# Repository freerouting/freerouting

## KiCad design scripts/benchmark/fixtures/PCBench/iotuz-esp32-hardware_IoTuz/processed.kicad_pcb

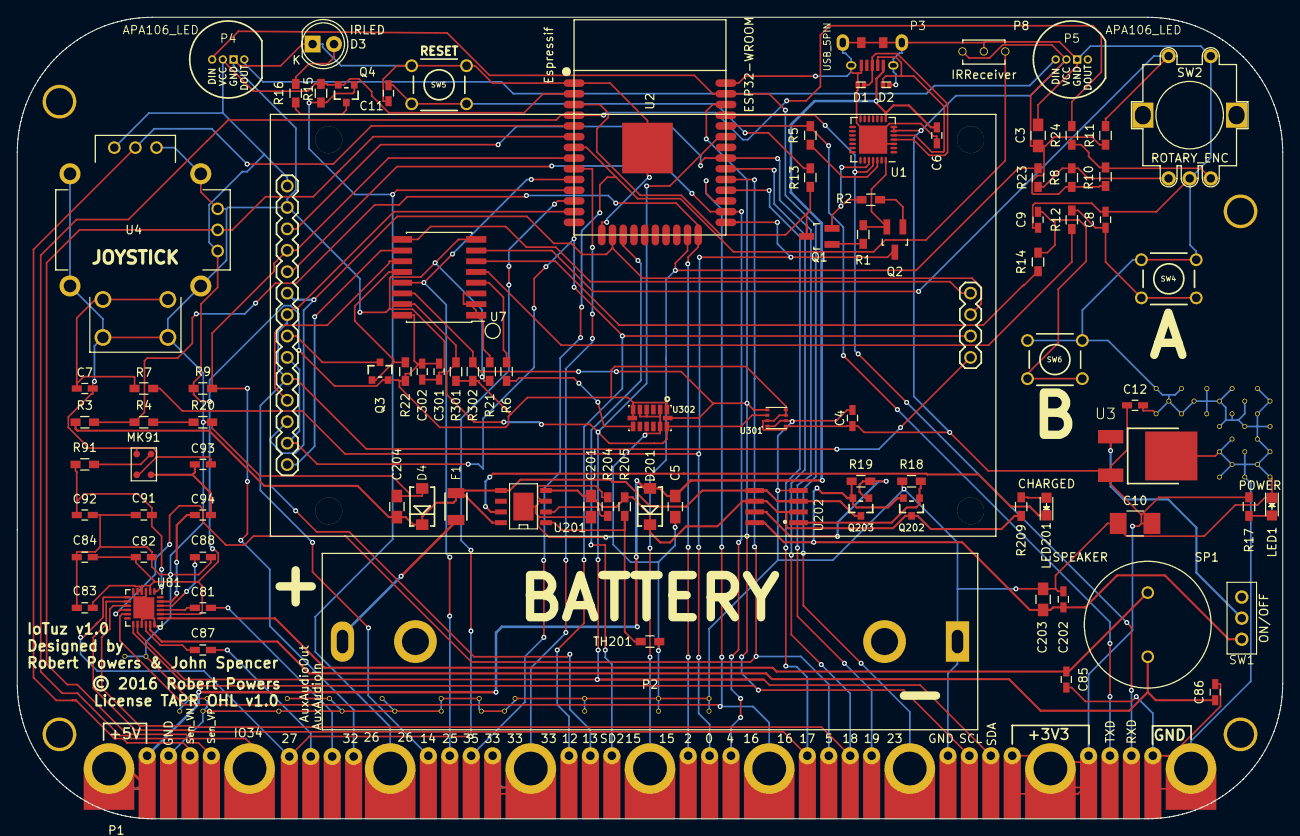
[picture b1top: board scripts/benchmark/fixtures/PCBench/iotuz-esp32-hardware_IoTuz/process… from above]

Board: 2 copper layers, 150.0 x 95.0 mm, 153 parts (0 on the bottom side), 82 nets.

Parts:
C3, C5, C201, C203, C204: 10uF 16V; C_0805_HandSoldering
C4, C6, C12, C202: 0.1uF; C_0603_HandSoldering
C7, C8, C9: 1nF; C_0603_HandSoldering
C10: 100uF 6.3V X5R; C_1210_HandSoldering
C11, C81, C87, C94, C301, C302: 1uF; C_0603_HandSoldering
C82, C83, C84, C88, C91: 4.7uF; C_0603_HandSoldering
C85, C86, C92, C93: 33pF 1%; C_0603_HandSoldering
D1, D2: ESD05V88D-LC; SOD-882
D3: IRLED; LED-5MM
D4, D201: SS14; DIODE_SMA
F1: 1A PTC; 1210
LED1: POWER; LED_0805
LED201: CHARGED; LED_0805
MK91: SPU0410HR5H; MEMSMicrophone-SMT-SPU0410HR5H‐PB
MP1, MP2, MP3, MP4: M3; MountingHole_3.2mm_M3.IoTuz
Noname_1, Noname_2, Noname_3, Noname_4, Noname_5, Noname_6, Noname_7, Noname_8, Noname_9, Noname_10, Noname_11, Noname_12, Noname_13, Noname_14, Noname_15, Noname_16, Noname_17, Noname_18, Noname_19, Noname_20, Noname_21, Noname_22, Noname_23, Noname_24, Noname_25, Noname_26, Noname_27, Noname_28, Noname_29, Noname_30, Noname_31, Noname_32, Noname_33, Noname_34, Noname_35, Noname_36, Noname_37, Noname_38, Noname_39, Noname_40, Noname_41, Noname_42, Noname_43, Noname_44, Noname_45, Noname_46, Noname_47, Noname_48, Noname_49, Noname_50, Noname_51, Noname_52: via.0.6mm-drill.0.4mm
P1: ALLIGATOR_X39; alligator_pads.x39.shortened
P2: BATTERY; BH-18650
P3: USB_5PIN; USB-MICRO-5pin_PTHMOUNT-Amphenol.10118194-0001LF
P4, P5: APA106_LED; LED_8MM_APA-106
P8: IRReceiver; TSOP38238.IRReceiver
Q1, Q2: S8050; SOT-23_Handsoldering
Q3, Q4, Q202, Q203: FDN340P; SOT23_FET
R1, R2: 12K(1%); R_0603_HandSoldering
R3: 1M; R_0603_HandSoldering
R4, R18, R19: 100K; R_0603_HandSoldering
R5, R7, R12, R13, R14, R17, R209: 470R(1%); R_0603_HandSoldering
R6, R8, R9, R10, R11, R15, R20, R21, R22, R23, R24: 10K; R_0603_HandSoldering
R16: 22R; R_0603_HandSoldering
R91: 1K; R_0603_HandSoldering
R204: 3.6K 1%; R_0603_HandSoldering
R205: 7.15K 1%; R_0603_HandSoldering
R301, R302: 4.7K; R_0603_HandSoldering
SP1: SPEAKER; CVS-1508.Speaker.PCPins
SW1: ON/OFF; SS12D00
SW2: ROTARY_ENC; EC11
SW4: A; SW_PUSHBUTTON_PTH
SW5: RESET; SW_PUSHBUTTON_PTH
SW6: B; SW_PUSHBUTTON_PTH
TH201: 10K NTC; R_0603_HandSoldering
U1: CP2102; QFN-28-1EP_5x5mm_Pitch0.5mm
U2: ESP32-WROOM
U3: NCP5501; DPAK3.NCP5501
U4: JOYSTICK; JOYSTICK_W_BUTTON
U6: ili9341.TouchLCD.Red.NoName; lcdtouchscreen.2.8inch-red.no-name.ili9341-xpt2046
U7: PCF8574; PCF8574.SOIC-16W_Pitch1.27mm
U81: NAU8814; NAU8814_QFN-24_4x4mm_Pitch0.5mm_EPAD
U201: CN3063; CN3063_SOIC8_EP
U202: MCP6002; SO08_4mm
U301: BME280
U302: ADXL345

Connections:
+3V3: C3.1, C4.1, C10.2, C12.1, C82.1, C83.1, C84.1, C301.1, C302.1, P1.5, P1.6, P1.7, P4.2, P5.2, P8.3, Q3.S, Q4.S, R8.2, R9.2, R10.2, R11.1, R15.1, R17.2, R22.1, R301.1, R302.1, U1.6, U1.7, U2.2, U3.3, U4.X1, U4.Y3, U6.1, U7.16, U81.2, U81.4, U81.5, U81.20, U301.2, U301.5, U301.6, U301.8, U302.1, U302.6, U302.7
+5V: C5.1, C6.1, D201.A, P1.38, P1.39, P3.1, U1.8
/ACCEL_INT: R6.1, U7.4
/A_Btn: R12.1, U7.5
/Audio/AUX: C81.1, U81.21
/Audio/MIC-: C94.1, U81.23
/Audio/MICBias: C91.1, C92.1, R91.2, U81.1
/Audio/Speaker+: C86.1, SP1.2, U81.17
/Audio/Speaker-: C85.1, SP1.1, U81.19
/AuxAudioIn: C81.2, P1.31
/BAT+: C204.1, D4.K, F1.2, Q203.D, R3.1, U201.5, U201.8, U202.3, U202.5
/BL_Control: Q3.G, R22.2, U7.12
/B_Btn: R14.1, U7.6
/DTR: Q2.2, R1.2, U1.28
/EN: Q1.3, R13.1, U2.3
/Enc_Btn: R11.2, SW2.4, U7.7
/I2C Sensors/ADXL_INT: R6.2, U302.8
/I2C_SCL: P1.9, R302.2, U2.36, U7.14, U81.13, U301.4, U302.14
/I2C_SDA: P1.8, R301.2, U2.33, U7.15, U81.14, U301.3, U302.13
/IO0: P1.18, Q2.3, R7.2, U2.25
/IO2: P1.19, R3.2, R4.2, U2.24
/IO4: P1.17, U2.26, U6.5
/IO5: P1.14, U2.29, U81.10
/IO12: P1.23, U2.14, U6.9, U6.13, U6.17
/IO13: P1.22, U2.16, U6.6, U6.12, U6.16
/IO14: P1.28, U2.13, U6.7, U6.10, U6.18
/IO15: P1.20, R23.2, U2.23
/IO16: P1.16, U2.27, U81.11
/IO17: P1.15, U2.28, U81.8
/IO18: P1.13, U2.30, U81.9
/IO19: P1.12, U2.31, U6.3
/IO23: P1.11, P4.1, U2.37
/IO25: P1.27, U2.10, U7.13
/IO26: P1.29, Q4.G, R15.2, U2.11
/IO27: P1.33, U2.12, U81.7
/IO32: P1.30, R9.1, U2.8, U6.4
/IO33: P1.24, P1.25, U2.9
/IO34: P1.34, U2.6, U4.X2
/IO35: P1.26, P8.1, U2.7
/MonoAudioOut: C87.1, P1.32
/Power/3.3V: C202.1, C203.1, Q202.S, Q203.S, R19.1, SW1.1, U202.8
/Power/3.3V_SWITCH: SW1.2, U3.1
/Power/GBAT: Q203.G, R19.2, U202.7
/Power/GIN: Q202.G, R18.1, U202.1
/Power/VIN: C201.1, D201.K, Q202.D, R205.1, R209.2, U201.4, U202.2, U202.6
/Power/~CHRG: LED201.1, U201.7
/RTS: Q1.2, R2.2, U1.24
/RXD: P1.3, U1.25, U2.35
/SD2: P1.21, U2.17
/SD_Sel: U6.15, U7.9
/Sensor_VN: P1.36, U2.5, U4.Y2
/Sensor_VP: P1.35, R24.2, U2.4
/TXD: P1.4, R5.1, U2.34
/Touch_INT: U6.14, U7.10
/Touch_Sel: U6.11, U7.11
/USB_D+: D1.2, P3.3, U1.4
/USB_D-: D2.2, P3.2, U1.5
GND: C3.2, C4.2, C5.2, C6.2, C7.2, C8.2, C9.2, C10.1, C11.2, C12.2, C82.2, C83.2, C84.2, C85.2, C86.2, C88.1, C91.2, C92.2, C93.2, C201.2, C202.2, C203.2, C204.2, C301.2, C302.2, D1.1, D2.1, D3.1, D4.A, LED1.1, MK91.2, MK91.3, Noname_1.1, Noname_2.1, Noname_3.1, Noname_4.1, Noname_5.1, Noname_6.1, Noname_7.1, Noname_8.1, Noname_9.1, Noname_10.1, Noname_11.1, Noname_12.1, Noname_13.1, Noname_14.1, Noname_15.1, Noname_16.1, Noname_17.1, Noname_18.1, Noname_19.1, Noname_20.1, Noname_21.1, Noname_22.1, Noname_23.1, Noname_24.1, Noname_25.1, Noname_26.1, Noname_27.1, Noname_28.1, Noname_29.1, Noname_30.1, Noname_31.1, Noname_32.1, Noname_33.1, Noname_34.1, Noname_35.1, Noname_36.1, Noname_37.1, Noname_38.1, Noname_39.1, Noname_40.1, Noname_41.1, Noname_42.1, Noname_43.1, Noname_44.1, Noname_45.1, Noname_46.1, Noname_47.1, Noname_48.1, Noname_49.1, Noname_50.1, Noname_51.1, Noname_52.1, P1.1, P1.2, P1.10, P1.37, P2.1, P3.5, P3.SHLD, P4.3, P5.3, P8.2, R18.2, R20.1, R21.2, R204.2, SW2.2, SW2.5, SW4.1, SW5.1, SW6.1, TH201.2, U1.3, U1.29, U2.1, U2.15, U2.38, U2.39, U3.2, U4.SH, U4.SW2, U4.X3, U4.Y1, U6.2, U7.8, U81.3, U81.6, U81.15, U81.18, U81.25, U201.3, U201.PAD, U202.4, U301.1, U301.7, U302.2, U302.4, U302.5, U302.12
unnamed: C7.1, R7.1, U4.SW1
unnamed: C8.1, R12.2, SW4.2
unnamed: C9.1, R14.2, SW6.2
unnamed: C11.1, R13.2, SW5.2
unnamed: C87.2, U81.16
unnamed: C88.2, U81.22
unnamed: C93.1, C94.2, MK91.4
unnamed: D3.2, R16.2
unnamed: F1.1, P2.2
unnamed: LED1.2, R17.1
unnamed: LED201.2, R209.1
unnamed: MK91.1, R91.1
unnamed: P4.4, P5.1
unnamed: Q1.1, R1.1
unnamed: Q2.1, R2.1
unnamed: Q3.D, U6.8
unnamed: Q4.D, R16.1
unnamed: R5.2, U1.26
unnamed: R10.1, R24.1, SW2.3
unnamed: R4.1, R20.2
unnamed: R21.1, U7.1, U7.2, U7.3
unnamed: R8.1, R23.1, SW2.1
unnamed: R204.1, U201.2
unnamed: R205.2, TH201.1, U201.1

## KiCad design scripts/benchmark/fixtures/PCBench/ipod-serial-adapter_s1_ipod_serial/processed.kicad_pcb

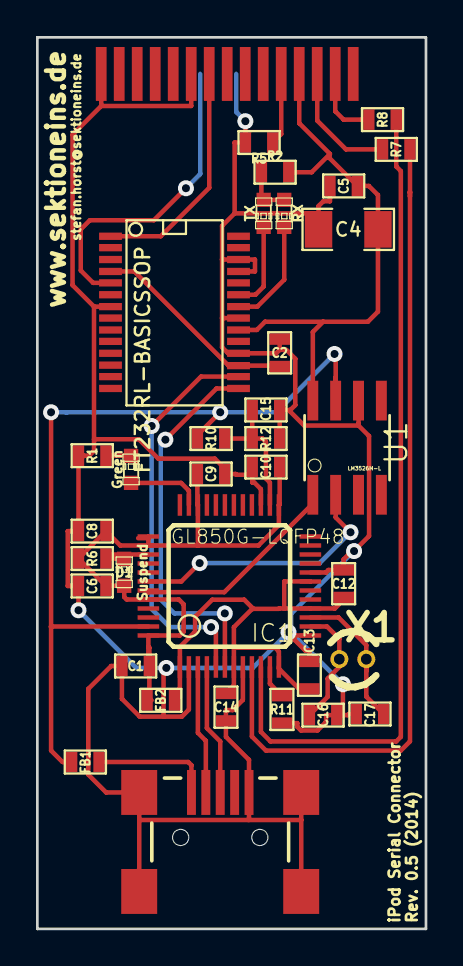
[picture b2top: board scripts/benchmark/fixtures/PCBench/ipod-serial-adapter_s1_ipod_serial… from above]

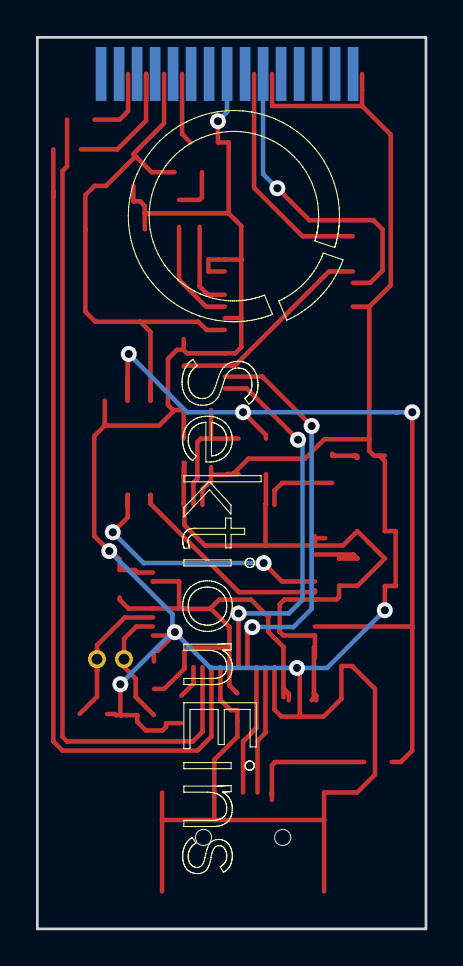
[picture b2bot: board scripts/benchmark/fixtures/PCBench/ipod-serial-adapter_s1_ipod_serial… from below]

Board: 2 copper layers, 21.6 x 49.5 mm, 36 parts (2 on the bottom side), 30 nets.

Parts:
C1: 10uF/10V; SM0603
C2, C5, C6, C8, C9, C10, C12, C13, C14: 100nF; SM0603
C4: 100uF; SM1206
C15: 1uF; SM0603
C16, C17: 20pF; SM0603
D1: Suspend; LED-0603
D2: Green; LED-0603
D3: RX; LED-0603
D4: TX; LED-0603
FB1, FB2: FILTER; SM0603
IC1: GL850G-LQFP48; LQFP48
J1: USB-MINIB-5PIN; USB-MINIB
P1: IPOD_CONNECTOR_MALE; IPOD_MALE_CONNECTOR
R1: 470R; SM0603
R2: 270R; SM0603
R5: 470K; SM0603
R6: 100K; SM0603
R7, R8: 0R; SM0603
R10: 10K; SM0603
R11: 680R; SM0603
R12: 47K; SM0603
SektionEinsLogo: VAL**; SektionEinsLogo
U1: LM3526M-L; SO08
U2: FT232RL-BASICSSOP; SSOP-28
X1: 12 Mhz; Crystal_Round_Vertical_3mm

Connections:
+5V: C4.1, C5.2, P1.23, R2.1, U1.8, U2.20
/HUB_IPOD_GREEN: D2.1, IC1.35
/IPOD_USB_D+: IC1.10, R8.2
/IPOD_USB_D-: IC1.9, R7.2
/OVCUR1: IC1.42, U1.2
/PWREN1: IC1.43, U1.1
/SERIAL_RX: P1.12, U2.5
/SERIAL_RX_LED: D3.2, U2.22
/SERIAL_TX: P1.13, U2.1
/SERIAL_TX_LED: D4.2, U2.23
/SERIAL_USB_D+: IC1.6, U2.15
/SERIAL_USB_D-: IC1.5, U2.16
/USB_D+: IC1.4, J1.D+
/USB_D-: IC1.3, J1.D-
AVDD: C12.1, C13.1, C14.1, FB2.2, IC1.1, IC1.7, IC1.12, IC1.16, IC1.19
DVDD: C1.1, C6.1, C8.1, C9.1, C10.1, D1.1, FB2.1, IC1.25, IC1.34, IC1.37, IC1.38, IC1.44, IC1.48, R6.2
GND: C1.2, C2.2, C4.2, C5.1, C6.2, C8.2, C9.2, C10.2, C12.2, C13.2, C14.2, C15.1, C16.2, C17.2, IC1.2, IC1.8, IC1.13, IC1.20, IC1.27, J1.GND, J1.MTN1, J1.MTN2, J1.MTN3, J1.MTN4, P1.1, P1.11, P1.16, R1.2, R5.1, R11.2, R12.1, U1.6, U2.7, U2.18, U2.21, U2.25, U2.26
unnamed: C2.1, U2.4, U2.17
unnamed: C15.2, IC1.26, R10.1, R12.2
unnamed: C16.1, IC1.14, X1.1
unnamed: C17.1, IC1.15, X1.2
unnamed: D1.2, IC1.39, R6.1
unnamed: D2.2, R1.1
unnamed: D3.1, D4.1, R2.2
unnamed: FB1.1, J1.VBUS
unnamed: IC1.11, R11.1
unnamed: P1.21, R5.2
unnamed: P1.25, R7.1
unnamed: P1.27, R8.1
VBUS: FB1.2, IC1.47, R10.2, U1.7

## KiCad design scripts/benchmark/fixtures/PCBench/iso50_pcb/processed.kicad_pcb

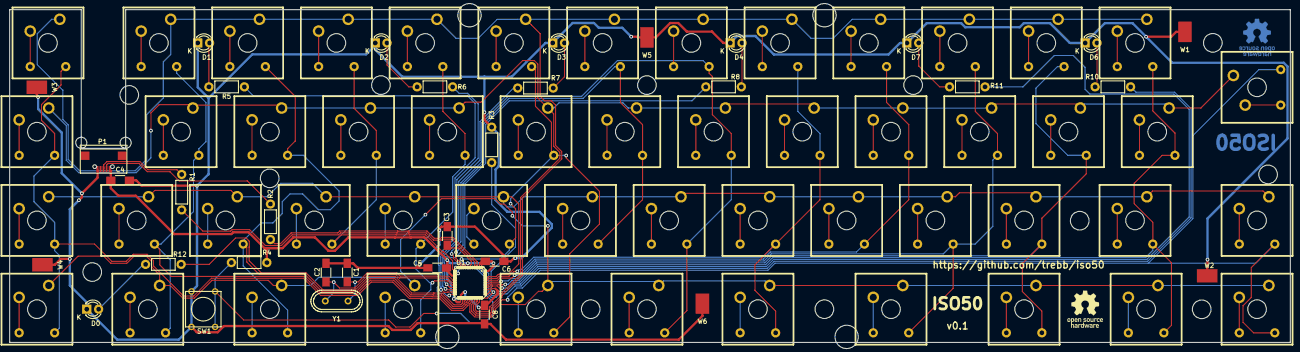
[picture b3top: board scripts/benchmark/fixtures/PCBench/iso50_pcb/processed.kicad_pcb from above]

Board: 2 copper layers, 274.9 x 71.4 mm, 87 parts (0 on the bottom side), 95 nets.

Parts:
C1, C2: 18p; C_1206_HandSoldering
C3, C4: 1u; C_1206_HandSoldering
C5, C6, C8: 100n; C_1206_HandSoldering
D0, D1, D2, D3, D4, D6, D7: Led_Small; LED-3MM
P1: USB; USB_Micro-207A-BBA0-R
R1, R2: 22; Resistor_Horizontal_RM7mm
R3, R4: 10k; Resistor_Horizontal_RM7mm
R5, R6, R7, R8, R10, R11, R12: 330; Resistor_Horizontal_RM7mm
SW1: SW_PUSH; SW_PUSH_SMALL
U00, U01, U02, U03, U04, U05, U06, U07, U08, U09, U10, U010, U11, U011, U12, U012, U13, U14, U15, U16, U17, U18, U19, U20, U21, U22, U23, U24, U25, U26, U27, U28, U29, U30, U31, U32, U34, U35, U37, U38, U110, U111, U112, U113, U210, U211, U212, U213, U310, U311, U312, U313: MX-DI; MXDIODE
U1: ATmega32U4; MLF-44_Atmel
W1, W2, W3, W4, W5, W6: TEST_1P; Spring-Contact_SMD
Y1: HC49S; Crystal_HC49-U_Vertical

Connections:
/col0: U00.4, U1.28, U10.4, U20.4, U30.4
/col1: U01.4, U1.27, U11.4, U21.4, U31.4
/col2: U1.26, U02.4, U12.4, U22.4, U32.4
/col3: U1.12, U03.4, U13.4, U23.4
/col4: U1.18, U04.4, U14.4, U24.4, U34.4
/col5: U1.8, U05.4, U15.4, U25.4, U35.4
/col6: U1.9, U06.4, U16.4, U26.4
/col7: U1.10, U07.4, U17.4, U27.4, U37.4
/col8: U1.40, U08.4, U18.4, U28.4, U38.4
/col9: U1.39, U09.4, U19.4, U29.4
/colA: U1.38, U010.4, U110.4, U210.4, U310.4
/colB: U1.37, U011.4, U111.4, U211.4, U311.4
/colC: U1.36, U012.4, U112.4, U212.4, U312.4
/colD: U1.30, U113.4, U213.4, U313.4
/led0: R12.2, U1.25
/led1: R5.2, U1.22
/led2: R6.2, U1.21
/led3: R7.2, U1.20
/led4: R8.2, U1.19
/led6: R10.2, U1.11
/led7: R11.2, U1.1
/row0: U00.2, U01.2, U1.31, U02.2, U03.2, U04.2, U05.2, U06.2, U07.2, U08.2, U09.2, U010.2, U011.2, U012.2
/row1: U1.32, U10.2, U11.2, U12.2, U13.2, U14.2, U15.2, U16.2, U17.2, U18.2, U19.2, U110.2, U111.2, U112.2, U113.2
/row2: U1.41, U20.2, U21.2, U22.2, U23.2, U24.2, U25.2, U26.2, U27.2, U28.2, U29.2, U210.2, U211.2, U212.2, U213.2
/row3: U1.29, U30.2, U31.2, U32.2, U34.2, U35.2, U37.2, U38.2, U310.2, U311.2, U312.2, U313.2
GND: C1.2, C2.2, C3.2, C4.2, C5.2, C6.2, C8.2, D0.1, D1.1, D2.1, D3.1, D4.1, D6.1, D7.1, P1.5, R3.2, SW1.2, W1.1, W2.1, W3.1, W4.1, W5.1, W6.1
unnamed: C1.1, U1.16, Y1.1
unnamed: C2.1, U1.17, Y1.2
unnamed: C3.1, U1.6
unnamed: D0.2, R12.1
unnamed: D1.2, R5.1
unnamed: D2.2, R6.1
unnamed: D3.2, R7.1
unnamed: D4.2, R8.1
unnamed: D6.2, R10.1
unnamed: D7.2, R11.1
unnamed: P1.2, R2.1
unnamed: P1.3, R1.1
unnamed: R1.2, U1.4
unnamed: R2.2, U1.3
unnamed: R3.1, U1.33
unnamed: R4.2, SW1.1, U1.13
unnamed: U00.1, U00.3
unnamed: U01.1, U01.3
unnamed: U02.1, U02.3
unnamed: U03.1, U03.3
unnamed: U04.1, U04.3
unnamed: U05.1, U05.3
unnamed: U06.1, U06.3
unnamed: U07.1, U07.3
unnamed: U08.1, U08.3
unnamed: U09.1, U09.3
unnamed: U10.1, U10.3
unnamed: U010.1, U010.3
unnamed: U11.1, U11.3
unnamed: U011.1, U011.3
unnamed: U12.1, U12.3
unnamed: U012.1, U012.3
unnamed: U13.1, U13.3
unnamed: U14.1, U14.3
unnamed: U15.1, U15.3
unnamed: U16.1, U16.3
unnamed: U17.1, U17.3
unnamed: U18.1, U18.3
unnamed: U19.1, U19.3
unnamed: U20.1, U20.3
unnamed: U21.1, U21.3
unnamed: U22.1, U22.3
unnamed: U23.1, U23.3
unnamed: U24.1, U24.3
unnamed: U25.1, U25.3
unnamed: U26.1, U26.3
unnamed: U27.1, U27.3
unnamed: U28.1, U28.3
unnamed: U29.1, U29.3
unnamed: U30.1, U30.3
unnamed: U31.1, U31.3
unnamed: U32.1, U32.3
unnamed: U34.1, U34.3
unnamed: U35.1, U35.3
unnamed: U37.1, U37.3
unnamed: U38.1, U38.3
unnamed: U110.1, U110.3
unnamed: U111.1, U111.3
unnamed: U112.1, U112.3
unnamed: U113.1, U113.3
unnamed: U210.1, U210.3
unnamed: U211.1, U211.3
unnamed: U212.1, U212.3
unnamed: U213.1, U213.3
unnamed: U310.1, U310.3
unnamed: U311.1, U311.3
unnamed: U312.1, U312.3
unnamed: U313.1, U313.3
VCC: C4.1, C5.1, C6.1, C8.1, P1.1, R4.1, U1.2, U1.7, U1.14, U1.24, U1.34, U1.44

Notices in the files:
scripts/benchmark/fixtures/PCBench/iotuz-esp32-hardware_IoTuz/processed.kicad_pcb:
© 2016 Robert Powers
